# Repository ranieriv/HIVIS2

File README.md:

# HIVIS Monitor 2.0

Self-hosted indoor air quality and acoustic monitoring system built on ESP32. Designed for schools, offices, and research environments where privacy and data ownership matter.

**Live dashboard:** [https://hvht.net](https://hvht.net)

---

## What it measures

| Metric | Sensor | Notes |
|--------|--------|-------|
| IAQ (Air Quality Index) | BME688 + BSEC2 | 0–500 scale, accuracy 0–3 |
| CO₂ equivalent | BME688 + BSEC2 | ppm |
| VOC (breath VOC) | BME688 + BSEC2 | ppm |
| Temperature | BME688 | °C |
| Humidity | BME688 | % RH |
| Noise level | INMP441 | dB SPL |
| Battery voltage | ADC (GPIO 36) | % + volts |

---

## Architecture

```
┌─────────────────────────────────────────────────────┐
│  ESP32 Device (battery-powered)                     │
│  BME688 · INMP441 · OLED · Button · Buzzer          │
└──────────────────┬──────────────────────────────────┘
                   │ MQTT TLS :8883 · HTTP :8090 (OTA)
                   ▼
┌─────────────────────────────────────────────────────┐
│  Server (Docker)                                    │
│  Mosquitto → Node-RED → InfluxDB → Grafana          │
│  Nginx (https://hvht.net) · OTA server (:8090)      │
└─────────────────────────────────────────────────────┘
```

---

## Hardware

| Component | Part |
|-----------|------|
| MCU | ESP32 DOIT DevKit V1 |
| Air quality | Bosch BME688 breakout |
| Microphone | INMP441 I2S breakout |
| Display | 0.96" OLED SSD1306 (I2C) |
| Button | Tactile switch (GPIO 4) |
| Buzzer | Passive piezo (GPIO 25) |
| Power | 1S LiPo + USB-C charging module |

KiCad schematic, PCB layout, Gerber files, and BOM are in [`hardware/`](hardware/).

### GPIO Map

| GPIO | Function |
|------|----------|
| 21 | I2C SDA (BME688 + OLED) |
| 22 | I2C SCL (BME688 + OLED) |
| 12 | I2S WS — microphone |
| 13 | I2S LR — microphone channel select |
| 14 | I2S SCK — microphone |
| 26 | I2S SD — microphone data |
| 4  | Button (INPUT_PULLUP, active LOW) |
| 25 | Buzzer (LEDC PWM) |
| 36 | Battery ADC (voltage divider ×2.2) |

---

## Firmware

Built with PlatformIO (Arduino framework).

**Dependencies** (auto-installed via `platformio.ini`):
- `boschsensortec/bsec2` — IAQ/CO₂/VOC
- `olikraus/U8g2` — OLED display
- `bblanchon/ArduinoJson`
- `knolleary/PubSubClient` — MQTT
- `tzapu/WiFiManager` — captive portal provisioning

**Build and flash:**
```bash
# Install PlatformIO CLI or use the VS Code extension
pio run --target upload

# Upload LittleFS (config.json, bsec_state.bin)
pio run --target uploadfs
```

**First boot:** the device launches a captive portal (`HIVIS-Setup-XXXX`). Connect and enter your WiFi credentials and MQTT server address.

Device configuration lives in [`data/config.json`](data/config.json). All pin assignments and thresholds are overridable there without reflashing.

---

## Server

The full server stack runs on Docker. A single Linux machine is enough (tested on a Lenovo ThinkPad X200 with Ubuntu).

**Services:**

| Container | Purpose | Port |
|-----------|---------|------|
| `hivis-mosquitto` | MQTT broker (TLS) | 8883 |
| `hivis-nodered` | Data routing + device provisioning | 1880 |
| `hivis-influxdb` | Time-series storage | 8086 |
| `hivis-grafana` | Dashboards | 3000 |
| `hivis-ota` | Firmware update server | 8090 |
| `hivis-nginx` | Public HTTPS dashboard | 80, 443 |
| `hivis-certbot` | Let's Encrypt auto-renewal | — |

**Deploy:**
```bash
cd server
cp mosquitto/config/passwd.example mosquitto/config/passwd  # create credentials
docker compose up -d
```

See [`docs/system-overview.md`](docs/system-overview.md) for the full setup and [`docs/operations-manual.md`](docs/operations-manual.md) for day-to-day operations.

---

## Button functions

| Press | Duration | Action |
|-------|----------|--------|
| Short | < 400 ms | Next display page |
| Double | 2× within 400 ms | Stop alert buzzer |
| Long | 2–5 s | Launch reconfigure portal |
| Factory reset | > 5 s | Wipe NVS credentials and reboot |

---

## Documentation

| File | Contents |
|------|----------|
| [`docs/system-overview.md`](docs/system-overview.md) | Architecture, pin map, boot sequence, MQTT topics, server stack |
| [`docs/operations-manual.md`](docs/operations-manual.md) | Quick checks, troubleshooting, deploying firmware, adding devices |
| [`spec/01_device_firmware.md`](spec/01_device_firmware.md) | Firmware module details |
| [`spec/02_provisioning.md`](spec/02_provisioning.md) | First-boot captive portal and MQTT registration flow |
| [`spec/03_ota.md`](spec/03_ota.md) | OTA update system |
| [`spec/04_mqtt_data.md`](spec/04_mqtt_data.md) | MQTT topics and JSON payload schema |
| [`spec/05_server_infrastructure.md`](spec/05_server_infrastructure.md) | Docker stack and Mosquitto ACL |
| [`spec/06_grafana_dashboards.md`](spec/06_grafana_dashboards.md) | Dashboard definitions |

---

## Project structure

```
hivis2/
├── src/            # ESP32 firmware (C++/Arduino)
├── data/           # LittleFS filesystem (config.json)
├── hardware/       # KiCad schematic, PCB, Gerbers, BOM
├── server/         # Docker stack, Mosquitto, Node-RED, Grafana, Nginx
├── docs/           # Operations manual + system overview
├── spec/           # Detailed technical specifications
├── partitions.csv  # ESP32 flash partition table
└── platformio.ini  # Build configuration
```

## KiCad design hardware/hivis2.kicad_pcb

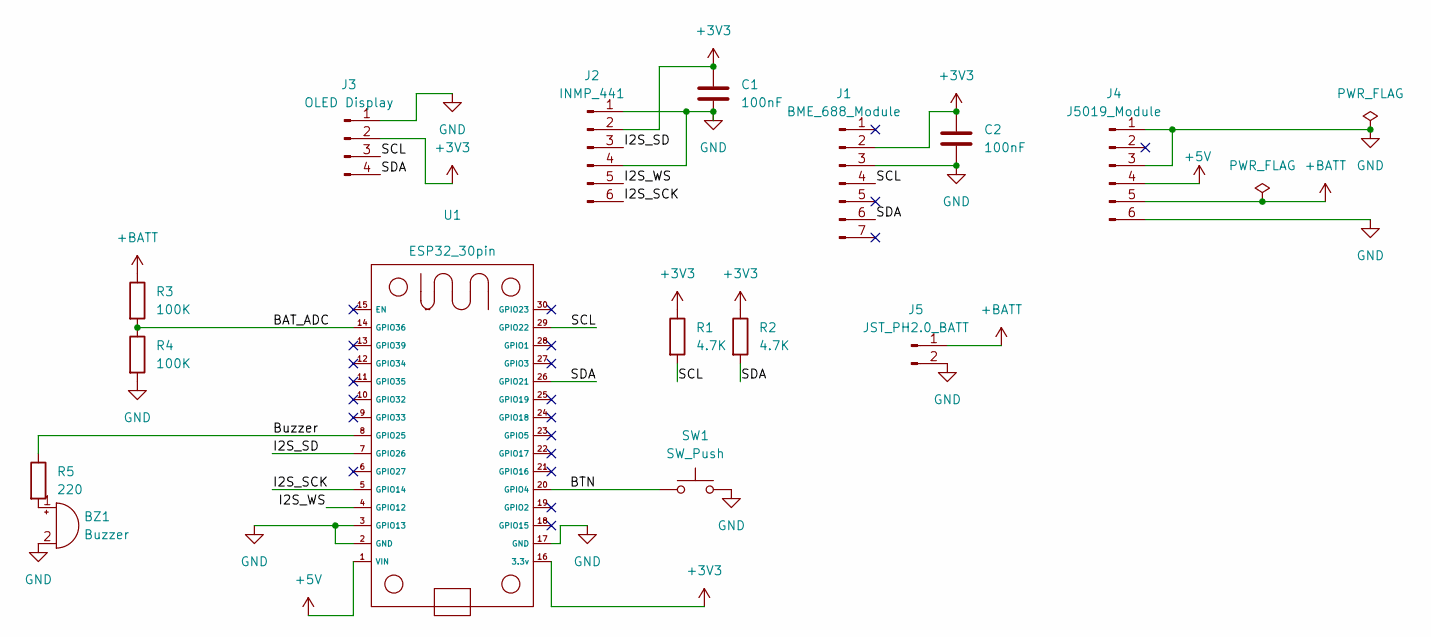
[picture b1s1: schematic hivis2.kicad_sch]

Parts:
BZ1: Buzzer; Buzzer_TDK_PS1240P02BT_D12.2mm_H6.5mm
C1, C2: 100nF; C_Disc_D5.0mm_W2.5mm_P5.00mm
J1: BME_688_Module; BME688_Breakout_7pin
J2: INMP_441; INMP441_Breakout_8mm
J3: OLED Display; OLED_SSD1306_27x27
J4: J5019_Module
J5: JST_PH2.0_BATT; JST_PH_B2B-PH-K_1x02_P2.00mm_Vertical
R1, R2: 4.7K; R_Axial_DIN0204_L3.6mm_D1.6mm_P7.62mm_Horizontal
R3, R4: 100K; R_Axial_DIN0204_L3.6mm_D1.6mm_P7.62mm_Horizontal
R5: 220; R_Axial_DIN0204_L3.6mm_D1.6mm_P7.62mm_Horizontal
SW1: SW_Push; SW_PUSH_6mm
U1: ESP32_30pin

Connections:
+3V3: C1.1, C2.1, J1.2, J2.2, J3.2, R1.1, R2.1, U1.16 (3.3v)
+5V: J4.4, U1.1 (VIN)
+BATT: J4.5, J5.1, R3.1
/BAT_ADC: R3.2, R4.1, U1.14 (GPIO36)
/BTN: SW1.1, U1.20 (GPIO4)
/Buzzer: R5.1, U1.8 (GPIO25)
/I2S_SCK: J2.6, U1.5 (GPIO14)
/I2S_SD: J2.3, U1.7 (GPIO26)
/I2S_WS: J2.5, U1.4 (GPIO12)
/SCL: J1.4, J3.3, R1.2, U1.29 (GPIO22)
/SDA: J1.6, J3.4, R2.2, U1.26 (GPIO21)
GND: BZ1.2 (-), C1.2, C2.2, J1.3, J2.1, J2.4, J3.1, J4.1, J4.3, J4.6, J5.2, R4.2, SW1.2, U1.2 (GND), U1.3 (GPIO13), U1.17 (GND)
unnamed: BZ1.1 (+), R5.2

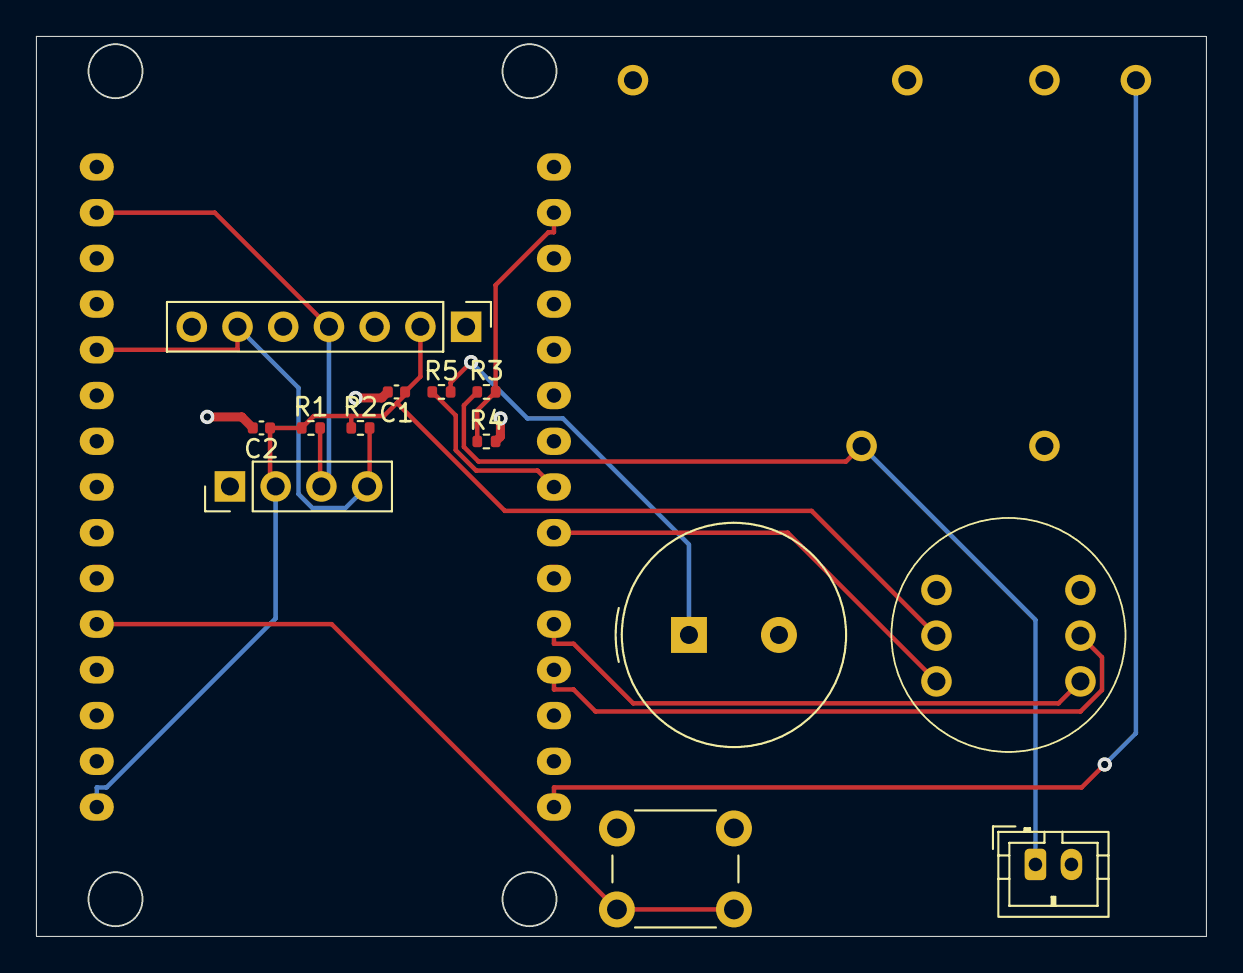
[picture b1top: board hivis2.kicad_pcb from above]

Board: 2 copper layers, 65.0 x 50.0 mm, 15 parts (1 on the bottom side), 13 nets.

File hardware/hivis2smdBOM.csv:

"Id";"Designator";"Footprint";"Quantity";"Designation";"Supplier and ref";
1;"R5";"R_0402_1005Metric";1;"220";;;
2;"R4,R3";"R_0402_1005Metric";2;"100K";;;
3;"R2,R1";"R_0402_1005Metric";2;"4.7K";;;
4;"C2,C1";"C_0402_1005Metric";2;"100nF";;;
5;"U1";"ESP32_30pin";1;"~";;;
6;"SW1";"SW_PUSH_6mm";1;"SW_Push";;;
7;"BZ1";"Buzzer_TDK_PS1240P02BT_D12.2mm_H6.5mm";1;"Buzzer";;;
8;"J4";"J5019_Module";1;"J5019_Module";;;
9;"J5";"JST_PH_B2B-PH-K_1x02_P2.00mm_Vertical";1;"BATT JST";;;
10;"J1";"BME688_Breakout_7pin";1;"BME_688_Module";;;
11;"J2";"INMP441_Breakout_8mm";1;"INMP_441";;;
12;"J3";"OLED_SSD1306_27x27";1;"OLED Display";;;

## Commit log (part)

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2026-04-27 Replace remaining internal IPs in spec files
